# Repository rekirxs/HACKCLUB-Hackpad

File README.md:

# HACKCLUB‑Hackpad

A compact macropad project including PCB, schematic, and a fitted case inspired by Serial Experiments Lain.

**Overview**

This repository contains the design files, a simple KMK firmware, and placeholder screenshots for a small 8-key macropad with rotary encoder, underglow LEDs, and a 0.91" OLED.

**Screenshots**

**Bill of Materials (BOM)**
- Seeed XIAO RP2040 — x1
- Through-hole 1N4148 diodes — x8
- MX-style mechanical switches — x8
- EC11 rotary encoder — x1
- Blank DSA keycaps — x8
- SK6812 MINI-E LEDs — x8
- 0.91 inch OLED display — x1
- M3 x 16 mm screws & M3 heat-set inserts — x4

**Repository layout**
- `cad/` — CAD files and case models
- `pcb/` — KiCad schematic and PCB files
- `firmware/` — KMK firmware and `keymap.py`
- `docs/images/` — project screenshots used by this README

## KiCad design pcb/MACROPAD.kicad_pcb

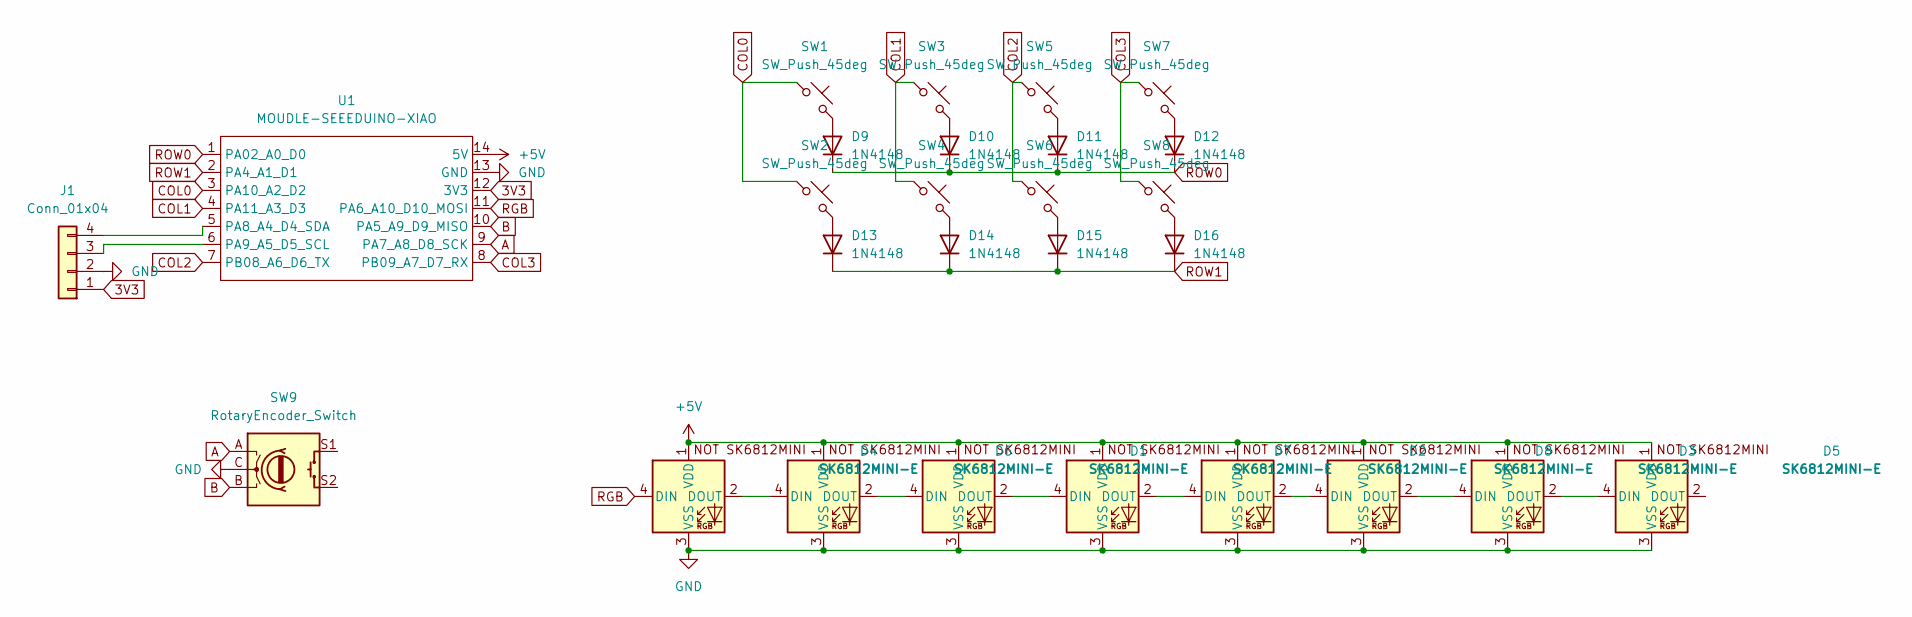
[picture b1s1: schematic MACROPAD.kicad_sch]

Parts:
D1, D2, D3, D4, D5, D6, D7, D8: SK6812MINI-E; SK6812MINI-E_fixed
D9, D10, D11, D12, D13, D14, D15, D16: 1N4148; D_DO-35_SOD27_P7.62mm_Horizontal
J1: Conn_01x04; PinHeader_1x04_P2.54mm_Vertical
SW1, SW2, SW3, SW4, SW5, SW6, SW7, SW8: SW_Push_45deg; SW_Cherry_MX_1.00u_PCB
SW9: RotaryEncoder_Switch; RotaryEncoder_Alps_EC11E-Switch_Vertical_H20mm
U1: MOUDLE-SEEEDUINO-XIAO; XIAO-Generic-Hybrid-14P-2.54-21X17.8MM

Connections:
3V3: J1.1, U1.12 (3V3)
+5V: D1.1 (VDD), D2.1 (VDD), D3.1 (VDD), D4.1 (VDD), D5.1 (VDD), D6.1 (VDD), D7.1 (VDD), D8.1 (VDD), U1.14 (5V)
A: SW9.A, U1.9 (PA7_A8_D8_SCK)
B: SW9.B, U1.10 (PA5_A9_D9_MISO)
COL0: SW1.1, SW2.1, U1.3 (PA10_A2_D2)
COL1: SW3.1, SW4.1, U1.4 (PA11_A3_D3)
COL2: SW5.1, SW6.1, U1.7 (PB08_A6_D6_TX)
COL3: SW7.1, SW8.1, U1.8 (PB09_A7_D7_RX)
GND: D1.3 (VSS), D2.3 (VSS), D3.3 (VSS), D4.3 (VSS), D5.3 (VSS), D6.3 (VSS), D7.3 (VSS), D8.3 (VSS), J1.2, SW9.C, U1.13 (GND)
unnamed: D1.4 (DIN), D6.2 (DOUT)
unnamed: D1.2 (DOUT), D7.4 (DIN)
unnamed: D2.4 (DIN), D7.2 (DOUT)
unnamed: D2.2 (DOUT), D8.4 (DIN)
unnamed: D3.4 (DIN), D8.2 (DOUT)
unnamed: D3.2 (DOUT), D5.4 (DIN)
unnamed: D4.2 (DOUT), D6.4 (DIN)
unnamed: D9.2 (A), SW1.2
unnamed: D10.2 (A), SW3.2
unnamed: D11.2 (A), SW5.2
unnamed: D12.2 (A), SW7.2
unnamed: D13.2 (A), SW2.2
unnamed: D14.2 (A), SW4.2
unnamed: D15.2 (A), SW6.2
unnamed: D16.2 (A), SW8.2
unnamed: J1.3, U1.6 (PA9_A5_D5_SCL)
unnamed: J1.4, U1.5 (PA8_A4_D4_SDA)
RGB: D4.4 (DIN), U1.11 (PA6_A10_D10_MOSI)
ROW0: D9.1 (K), D10.1 (K), D11.1 (K), D12.1 (K), U1.1 (PA02_A0_D0)
ROW1: D13.1 (K), D14.1 (K), D15.1 (K), D16.1 (K), U1.2 (PA4_A1_D1)

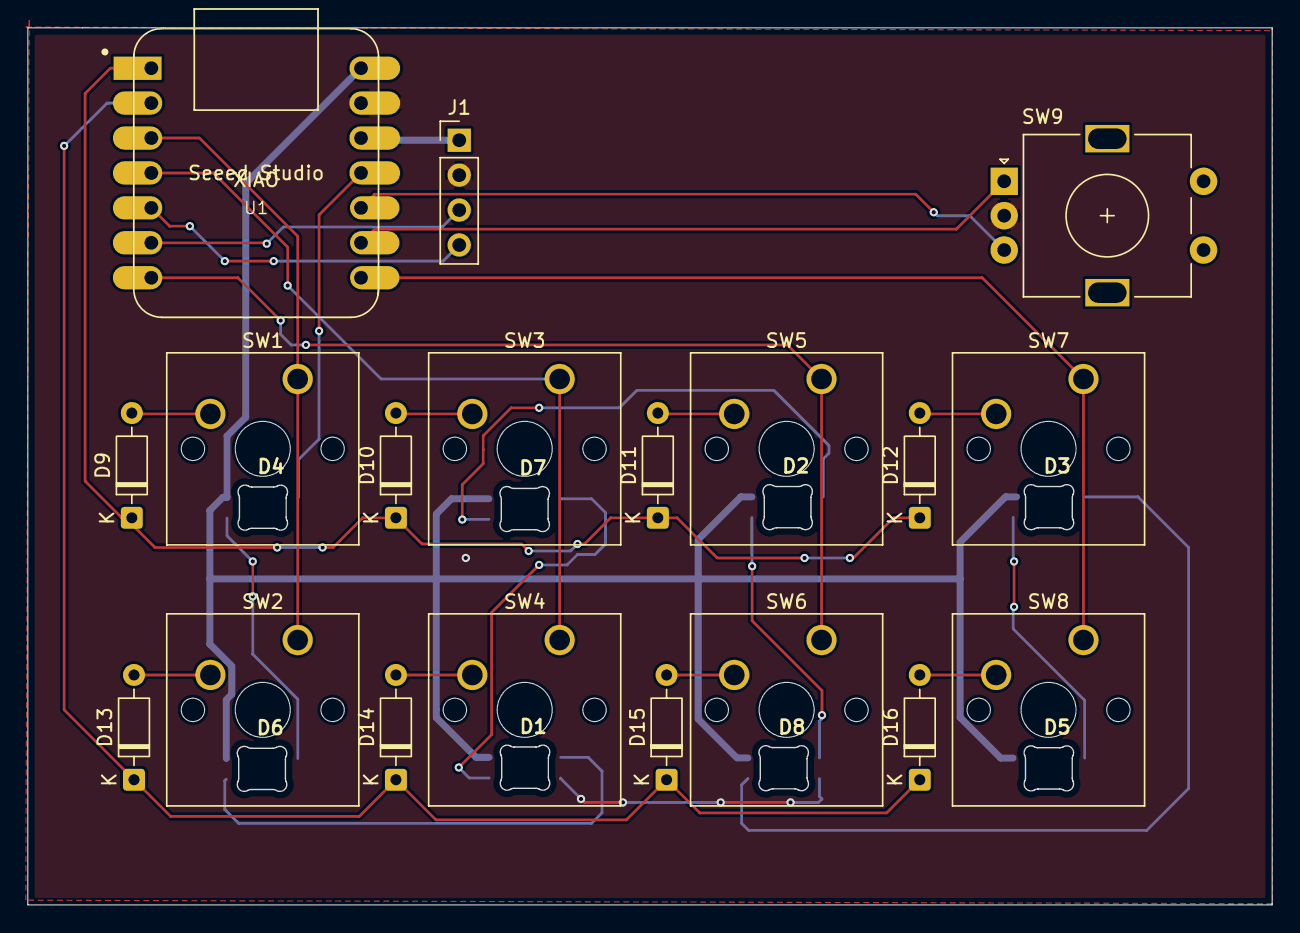
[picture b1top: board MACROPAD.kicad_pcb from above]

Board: 2 copper layers, 90.5 x 63.8 mm, 27 parts (0 on the bottom side), 29 nets.

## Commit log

2026-01-02 Add project screenshots
2026-01-02 Update README: overview, build instructions, fix image path
2026-01-02 Update README and add placeholders
2026-01-02 Add/replace project screenshots and update README
